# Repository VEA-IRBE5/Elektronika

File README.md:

# Elektronika
Zondes iespiedplašu trasēšana un darbs ar elektroniskām komponentēm

# Git bash konfigurācija un lokālās repozitorijas izveide

### 1. Instalē git bash

### 2. Izveido mapi, kurā glabās projektu

### 3. R-click(otrais peles taustiņš) -> Git bash here
  - Ja nerāda, atver git bash un ar cd navigē uz izveidoto mapi

### 4. Konsolē: git config --global user.name "Vards Uzvards" 
- git config --global user.email "epasts@mail.com"
  - Izmanto to epastu, kurš piesaistīts profilam, kas var tikt klāt IRBE5 repozitorijai
  - Var pārbaudīt, vai pareizi saglabāts ar tām pašām komandām, noņemot "" specificētos datus

### 5. (Neobligāts)Konsolē: git config --global core.editor "'C:/Program Files/Notepad++/notepad++.exe' -multiInst -notabbar -nosession -noPlugin"
  - var uzstādīt notepad++ kā default teksta editoru, kad raksta commit komentāru
  - Iesaku izdarīt, jo konsoles teksta editors nav ērts

### 6. Konsolē: git config --global init.defaultBranch main
- Citādi defaults būs master, un tas var radīt problēmas

### 7. Konsolē: git config --list
- Ar šo var pārbaudīt git bash konfigurāciju

### 8. Beidzot inicializē lokālo repozitoriju: git init

# Darbība ar lokālo github repositoriju

### 1. Konsolē: git remote add IRBE5 https://github.com/VEA-IRBE5/Elektronika.git
- turpmāk pie git pull var izmantot IRBE5 nevis pilno linku 
- ar šo pastās, vai sarakstā ir Konsolē: git remote -v

### 2. Konsolē: git pull IRBE5 [Branch name]
- Lejupielādē norādītā zara saturu no repozitorijas, par zaru lietošanu konsultējies ar nodaļas galveno

### 3. Pēc pašreizējās darba tūres beigšanas neaizmirsti izveidot commit, lai dati nepazūd
- Konsolē: git add . (vai git add "filename", ja negrib visas izmaiņas pievienot)
- Konsolē: git status (pastās, vai viss ir ok)
- Konsolē: git commit (Lūdzu izsmeļoši un ne pārāk gari aprakstiet izmainīto)(var izmantot: -m "Text here")
   
### 4. Kad liekas, ka pašreizējais uzdevums ir gana labā stāvoklī, Konsolē: git push IRBE5 [Branch name]

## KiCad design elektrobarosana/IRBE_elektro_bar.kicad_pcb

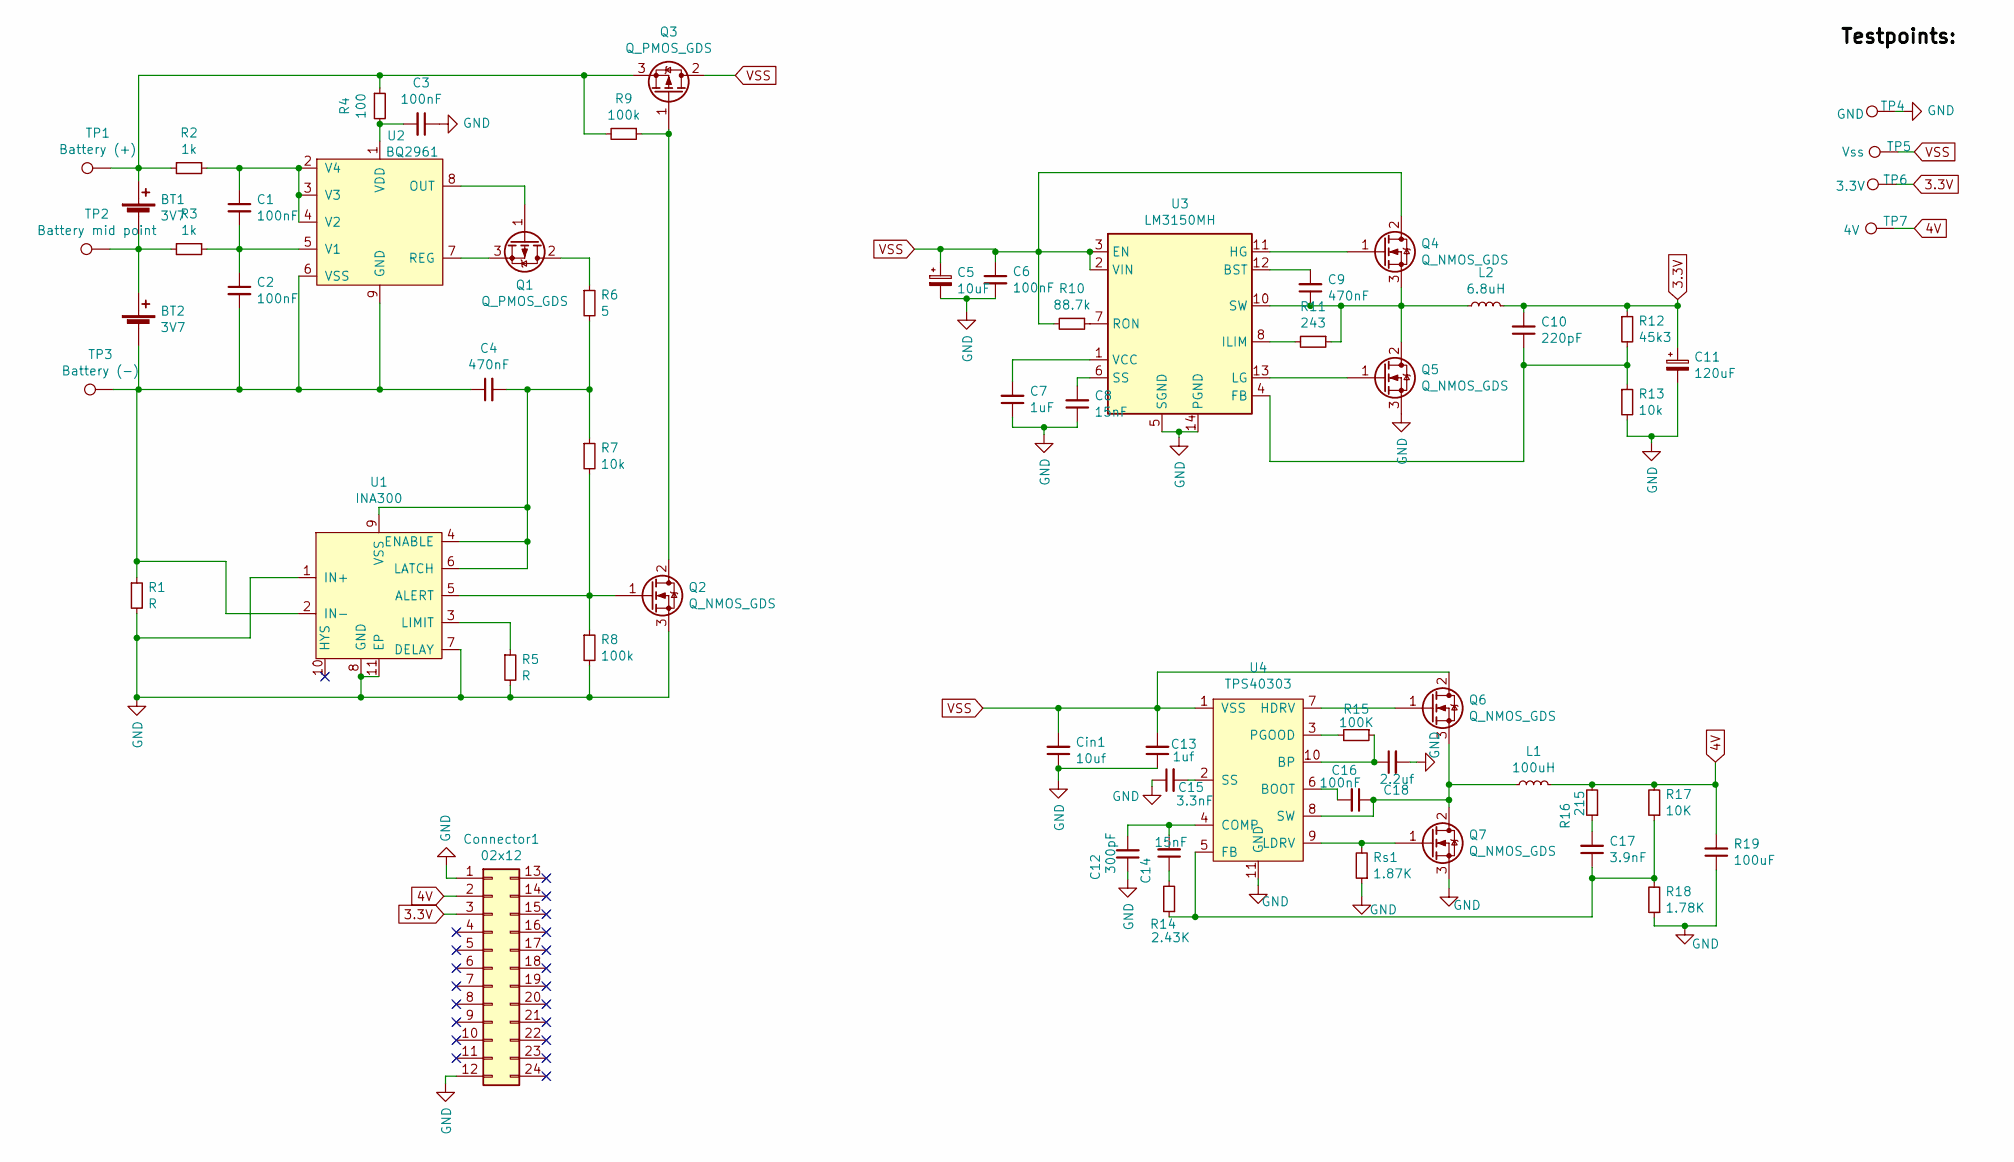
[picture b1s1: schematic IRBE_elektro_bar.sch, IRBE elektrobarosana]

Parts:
BT1, BT2: 3V7; R_Axial_DIN0204_L3.6mm_D1.6mm_P2.54mm_Vertical
C1, C2, C3, C6, C16: 100nF; C_0603_1608Metric_Pad1.08x0.95mm_HandSolder
C4, C9: 470nF; C_0603_1608Metric_Pad1.08x0.95mm_HandSolder
C5: 10uF; C_1206_3216Metric_Pad1.33x1.80mm_HandSolder
C7: 1uF; C_0603_1608Metric_Pad1.08x0.95mm_HandSolder
C8, C14: 15nF; C_0603_1608Metric_Pad1.08x0.95mm_HandSolder
C10: 220pF; C_0603_1608Metric_Pad1.08x0.95mm_HandSolder
C11: 120uF; CP_Elec_6.3x9.9
C12: 300pF; C_0603_1608Metric_Pad1.08x0.95mm_HandSolder
C13: 1uf; C_0603_1608Metric_Pad1.08x0.95mm_HandSolder
C15: 3.3nF; C_0603_1608Metric_Pad1.08x0.95mm_HandSolder
C17: 3.9nF; C_0603_1608Metric_Pad1.08x0.95mm_HandSolder
C18: 2.2uf; C_0603_1608Metric_Pad1.08x0.95mm_HandSolder
Cin1: 10uf; C_0603_1608Metric_Pad1.08x0.95mm_HandSolder
Connector1: 02x12; SAMTEC-SSW-112-02-X-D-RA
L1: 100uH; spole
L2: 6.8uH; spole
Q1, Q3: Q_PMOS_GDS; TO-252-2
Q2, Q4, Q5, Q6, Q7: Q_NMOS_GDS; TO-252-2
R1, R5: R; R_0603_1608Metric_Pad0.98x0.95mm_HandSolder
R2, R3: 1k; R_0603_1608Metric_Pad0.98x0.95mm_HandSolder
R4: 100; R_0603_1608Metric_Pad0.98x0.95mm_HandSolder
R6: 5; R_0603_1608Metric_Pad0.98x0.95mm_HandSolder
R7, R13: 10k; R_0603_1608Metric_Pad0.98x0.95mm_HandSolder
R8, R9: 100k; R_0603_1608Metric_Pad0.98x0.95mm_HandSolder
R10: 88.7k; R_0603_1608Metric_Pad0.98x0.95mm_HandSolder
R11: 243; R_0603_1608Metric_Pad0.98x0.95mm_HandSolder
R12: 45k3; R_0603_1608Metric_Pad0.98x0.95mm_HandSolder
R14: 2.43K; R_0603_1608Metric_Pad0.98x0.95mm_HandSolder
R15: 100K; R_0603_1608Metric_Pad0.98x0.95mm_HandSolder
R16: 215; R_0603_1608Metric_Pad0.98x0.95mm_HandSolder
R17: 10K; R_0603_1608Metric_Pad0.98x0.95mm_HandSolder
R18: 1.78K; R_0603_1608Metric_Pad0.98x0.95mm_HandSolder
R19: 100uF; C_0805_2012Metric_Pad1.18x1.45mm_HandSolder
Rs1: 1.87K; R_0603_1608Metric_Pad0.98x0.95mm_HandSolder
TP1: Battery (+); PinHeader_1x01_P2.54mm_Vertical
TP2: Battery mid point; PinHeader_1x01_P2.54mm_Vertical
TP3: Battery (-); PinHeader_1x01_P2.54mm_Vertical
TP4: GND; PinHeader_1x01_P2.54mm_Vertical
TP5: Vss; PinHeader_1x01_P2.54mm_Vertical
TP6: 3.3V; PinHeader_1x01_P2.54mm_Vertical
TP7: 4V; PinHeader_1x01_P2.54mm_Vertical
U1: INA300
U2: BQ2961
U3: LM3150MH; LM3150MHNOPB
U4: TPS40303

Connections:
3.3V: C10.2, C11.1, Connector1.3, L2.2, R12.1, TP6.1
4V: Connector1.2, L1.2, R16.2, R17.2, R19.2, TP7.1
GND: C3.1, C5.2, C6.2, C7.1, C8.1, C11.2, C12.1, C13.1, C15.1, C18.2, Cin1.1, Connector1.1, Connector1.12, Q2.3 (S), Q5.3 (S), Q7.3 (S), R1.2, R5.2, R8.2, R13.2, R18.1, R19.1, Rs1.1, TP4.1, U1.1 (IN+), U1.7 (DELAY), U1.8 (GND), U1.11 (EP), U3.5 (SGND), U3.9 (SGND), U3.14 (PGND), U3.15 (SGND), U4.11 (GND)
unnamed: BT1.1 (+), Q3.3 (S), R2.2, R4.1, R9.2, TP1.1
unnamed: BT1.2 (-), BT2.1 (+), R3.2, TP2.1
unnamed: BT2.2 (-), C2.2, C4.1, R1.1, TP3.1, U1.2 (IN-), U2.6 (VSS), U2.9 (GND)
unnamed: C1.1, R2.1, U2.2 (V4), U2.3 (V3), U2.4 (V2)
unnamed: C1.2, C2.1, R3.1, U2.5 (V1)
unnamed: C3.2, R4.2, U2.1 (VDD)
unnamed: C4.2, R6.2, R7.1, U1.4 (ENABLE), U1.6 (LATCH), U1.9 (VSS)
unnamed: C7.2, U3.1 (VCC)
unnamed: C8.2, U3.6 (SS)
unnamed: C9.1, L2.1, Q4.3 (S), Q5.2 (D), R11.1, U3.10 (SW)
unnamed: C9.2, U3.12 (BST)
unnamed: C10.1, R12.2, R13.1, U3.4 (FB)
unnamed: C12.2, C14.2, U4.4 (COMP)
unnamed: C14.1, R14.2
unnamed: C15.2, U4.2 (SS)
unnamed: C16.1, L1.1, Q6.3 (S), Q7.2 (D), U4.8 (SW)
unnamed: C16.2, U4.6 (BOOT)
unnamed: C17.1, R14.1, R17.1, R18.2, U4.5 (FB)
unnamed: C17.2, R16.1
unnamed: C18.1, R15.1, U4.10 (BP)
unnamed: Q1.1 (G), U2.8 (OUT)
unnamed: Q1.2 (D), R6.1
unnamed: Q1.3 (S), U2.7 (REG)
unnamed: Q2.1 (G), R7.2, R8.1, U1.5 (ALERT)
unnamed: Q2.2 (D), Q3.1 (G), R9.1
unnamed: Q4.1 (G), U3.11 (HG)
unnamed: Q5.1 (G), U3.13 (LG)
unnamed: Q6.1 (G), U4.7 (HDRV)
unnamed: Q7.1 (G), Rs1.2, U4.9 (LDRV)
unnamed: R5.1, U1.3 (LIMIT)
unnamed: R10.1, U3.7 (RON)
unnamed: R11.2, U3.8 (ILIM)
unnamed: R15.2, U4.3 (PGOOD)
VSS: C5.1, C6.1, C13.2, Cin1.2, Q3.2 (D), Q4.2 (D), Q6.2 (D), R10.2, TP5.1, U3.2 (VIN), U3.3 (EN), U4.1 (VSS)

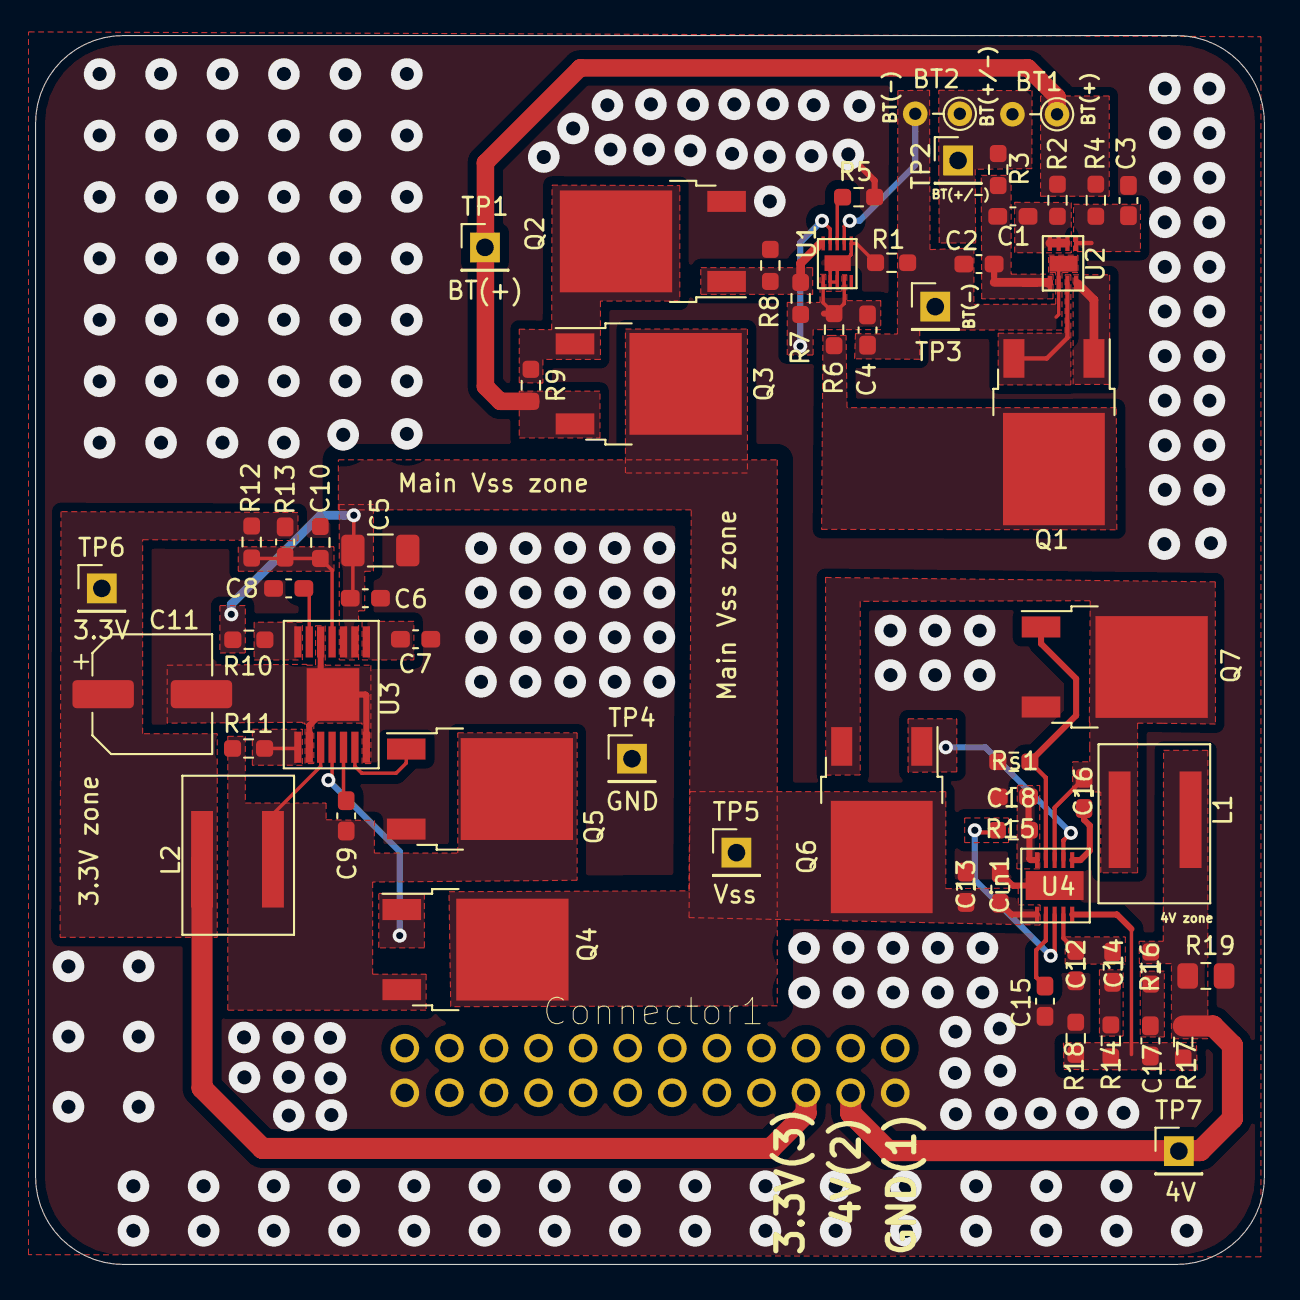
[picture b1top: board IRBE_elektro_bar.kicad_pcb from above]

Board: 2 copper layers, 70.0 x 70.0 mm, 62 parts (0 on the bottom side), 37 nets.

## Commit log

2021-09-20 README v1
2021-09-20 README uzlabojums
2021-10-11 elektrobarosanas plate 0.1
2021-10-18 Lugums apskatit plati
2022-04-15 Nepabeigtā COM programmējuma versija 0.1 V
2022-04-15 Izlabota GPS simbolu virkne, lai HUB varētu tos apstrādāt kā kordinātes
2022-04-20 v 0.2
2022-04-20 v 0.2 is it?
2022-04-24 v0.3
2022-05-15 v0.5 - GSM update
2022-05-15 v0.6 - microcontroler temperature
2022-05-22 kaut kas
2022-05-22 kaut kas2
2022-05-22 mareks v2
2022-05-22 mareks 0.3
2022-05-24 UART6 (communication with onboard/core mcu) receiving logic fixes Compiler code warning fixes
2022-05-26 Fixed XOR CCR.
2022-05-27 UART6 data receive logic bug fix No longer gets stuck after receiving data string with invalid checksum
2022-06-17 [GPS][INIT]
    - TODO
2022-06-19 [IRBE5-COM-KiCAD]
    -Pēdējā komunikācijas plates iespiedplates versija.
